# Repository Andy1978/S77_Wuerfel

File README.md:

# S77_Wuerfel
Elektronischer Würfel für den Section77 Lötkurs

http://tech-chat.de/files/VID_20150719_164159_Section77_Wuerfel.mp4

## Bauteile

Umgerechnet auf einen Bausatz

Anz. | Reichelt Bestellnummer | Bezeichnung                                | Preis
-----|------------------------|--------------------------------------------|-------
1    | ATTINY 13A-PU          | Atmel AVR-RISC-Controller                  | 0,99 €
7    | SLH 56 RT              | LED, 5mm, superhell, eingefärbt, klar, rot | 0,63 €
1    | BPW 40                 | Fototransistor, Plastikgehäuse, bedrahtet  | 0,29 €
7    | METALL 220             | Metallschichtwiderstand 220 Ohm            | 0,175 €
1    | METALL 12,0K           | Metallschichtwiderstand 12,0 K-Ohm         | 0,049 €
1    | GS 8P                  | IC-Sockel, 8-polig, superflach, gedreht, vergold. | 0,18 €
1    | TASTER 9302            | Kurzhubtaster 6x6mm, Höhe: 5,0mm, 12V, vertikal | 0,10 €
1    | H25SR160               | Streifenrasterplatine, Hartpapier, 160x100mm | 1,50 €, wird noch aufgeteilt
3    | aus GP AL40 AA         | Alkaline Mignon Aus 40er Pack              | 0,79€
1    | HALTER 3XUM3-DK        | Halter für 3 Mignonzellen (AA), Druckknopf | 0,40 €
1    | CLIP HQ9V-T            | Batterieclip für 9-Volt-Block, High-Quality, T-Form | 0,30€

## Abhängigkeiten unter GNU/Linux

* avr-gcc (Compiler für AVR µController)
* avr-libc
* avrdude (zum Übertragen der firmware)
* kicad (Für den Schaltplan)

In Debian basierten Distro z.B. über
```
sudo apt-get update
sudo apt-get install gcc-avr avr-libc avrdude kicad
```
zu installieren.

## Firmware compilieren und mit avrdude über USBasp flashen
```
cd src
make
make program
```

## udev rules für USBasp
```
$ cat /etc/udev/rules.d/45-avrusb.rules 
ATTRS{idVendor}=="16c0", ATTRS{idProduct}=="05dc", MODE="0660", GROUP="plugdev"
```

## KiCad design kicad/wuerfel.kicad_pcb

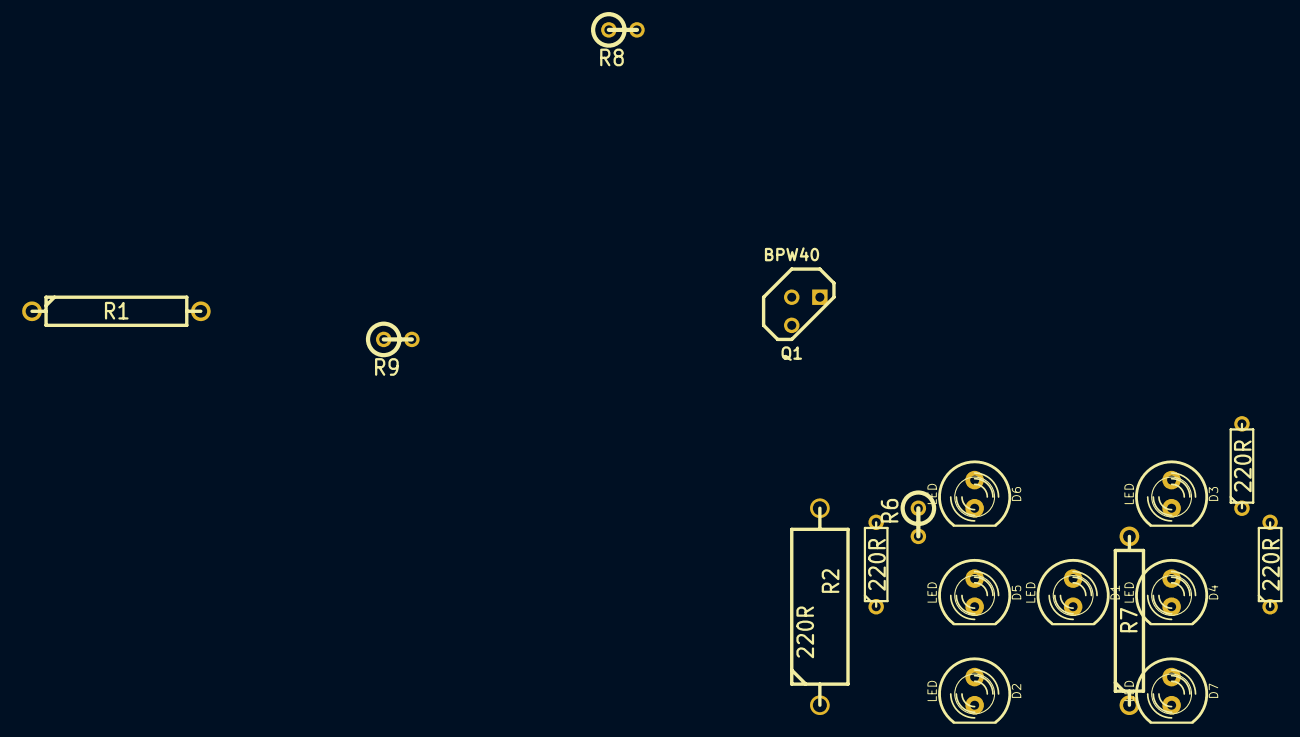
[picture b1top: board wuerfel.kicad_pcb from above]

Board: 2 copper layers, 17 parts (0 on the bottom side), 11 nets, no tracks yet.

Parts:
D1, D2, D3, D4, D5, D6, D7: LED; LED-5MM
Q1: BPW40; TO92
R1, R7: 220R; R6
R2: 220R; R7
R3, R4, R5: 220R; R3
R6: 220R; R1
R8: 12K; R1
R9: 10K; R1

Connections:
unnamed: D3.2, R3.1
unnamed: R4.2, R5.2
unnamed: D2.2, R2.1
unnamed: D4.2, R4.1
unnamed: D5.2, R5.1
unnamed: D1.2, R1.1
unnamed: D6.2, R6.1
unnamed: D7.2, R7.1
unnamed: R2.2, R3.2
unnamed: R6.2, R7.2
VCC: D1.1, D2.1, D3.1, D4.1, D5.1, D6.1, D7.1, R8.1, R9.1

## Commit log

2015-07-05 Fix tables in README
2015-07-06 Stub für firmware angelegt, Readme erweitert
2015-07-15 Lochraster Vorlage hinzugefügt
2015-07-19 Makefile MCU gefixt, erster LED Test
2015-07-19 Schalter aus Design entfernt, einfache Implementation fertiggestellt
2015-07-19 Use astyle for C source formatting
2015-07-19 KiCAD Zeichnungen erweitert (noch nicht fertig), Readme aktualisiert
2015-07-19 Link zum Demo Video hinzugefügt
2015-07-19 Bild des Aufbaus mit Unterbrechungen auf der Rückseite
2015-07-19 Auf A4 skaliert
2015-07-19 Make relative link
2015-07-22 udev rules hinzugefügt
2018-03-09 Fix Link to video
